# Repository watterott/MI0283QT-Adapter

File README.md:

# MI0283QT-Adapter
Adapter Board with 2.8" TFT-Display and Touchscreen/Touchpanel.

* Multi-Inno MI0283QT 2.8" Display with Touchpanel (320x240 pixel)
* Backlight dimmable
* 3.3V - 5V tolerant IOs
* Power: 3.3V - 5V
* **MI0283QT-Adapter v1**
  * TI ADS7846/TSC2046 Touch-Controller
  * Interface: SPI/SSI (8-Bit or 9-Bit, up to 32MHz)
* **MI0283QT-Adapter v2**
  * NXP LPC1114 ARM Cortex-M0 with Open-Source Firmware
  * Interface: UART, I2C, SPI/SSI (8-Bit, Mode 3, up to 4MHz)
  * Pin-compatible with MI0283QT-Adapter v1
* Open-Source and released under the [Creative Commons Attribution Share-Alike License](https://creativecommons.org/licenses/by-sa/4.0/).
* **[Documentation on learn.watterott.com](https://learn.watterott.com)**

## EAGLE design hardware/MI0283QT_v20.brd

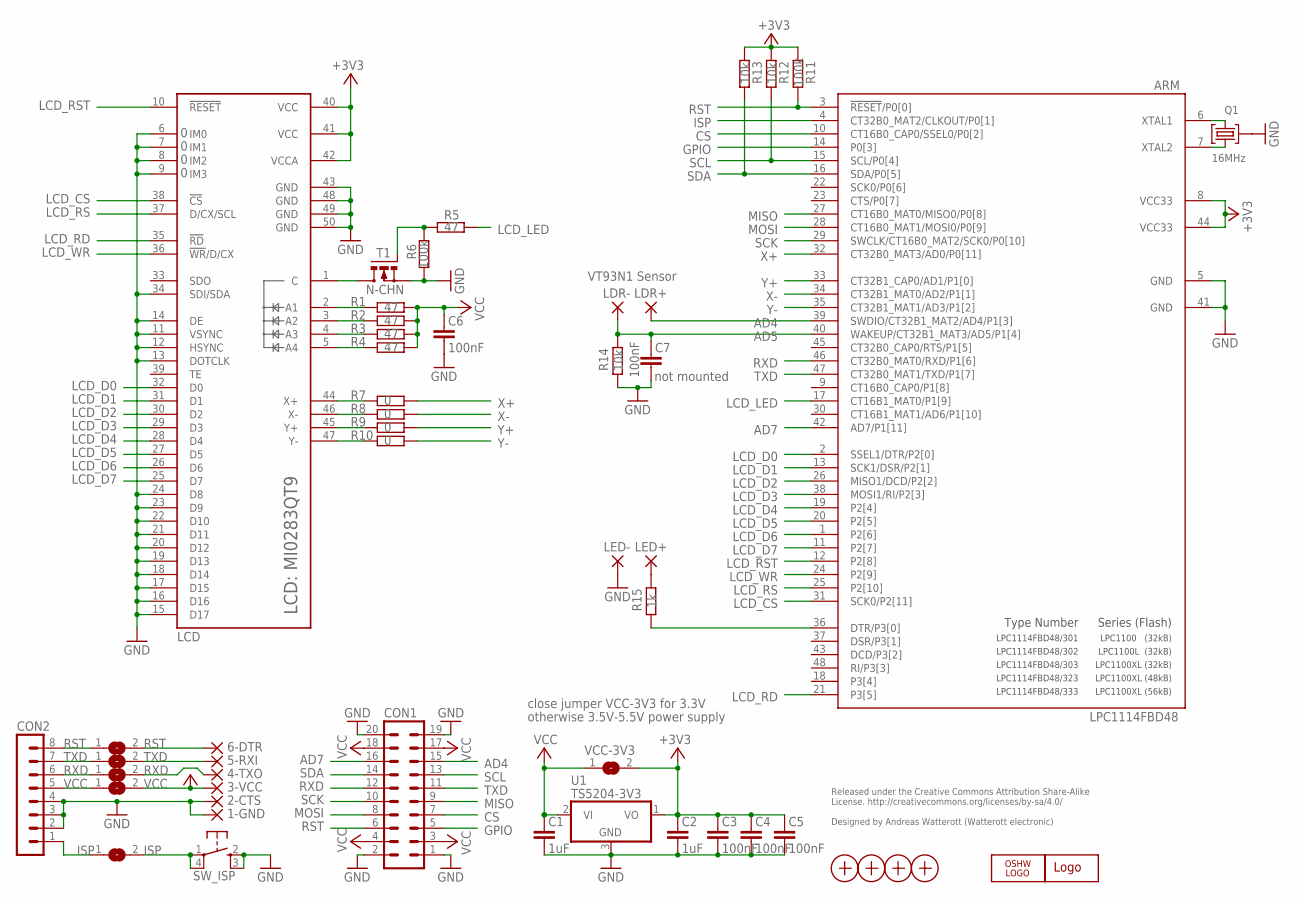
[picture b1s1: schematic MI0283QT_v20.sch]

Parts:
1-GND, 2-CTS, 3-VCC, 4-TXO, 5-RXI, 6-DTR: WIREPADSMD1,27-254; SMD1,27-2,54
ARM: LPC1114FBD48; LQFP48
C1, C2: 1uF; C0603
C3, C4, C5, C6, C7: 100nF; C0603
CON1: MA10-2
CON2: MA08-1
ISP: SJ
LCD: MI0283QT9
LDR+: WIREPAD2,15/1,0; 2,15/1,0
LDR-: WIREPAD2,15/1,0; 2,15/1,0
LED+: WIREPAD2,15/1,0; 2,15/1,0
LED-: WIREPAD2,15/1,0; 2,15/1,0
LOGO1: OSHW_LOGO_6MILX0150-NT; OSHW_6X150_NOTEXT
Q1: 16MHz; SMD_OSC_35X15
R1, R2, R3, R4, R5: 47; R0603
R6, R11: 100k; R0603
R7, R8, R9, R10: 0; R0603
R12, R13, R14: 10k; R0603
R15: 1k; R0603
RST: SJ
RXD: SJ
SW_ISP: SW_SMDS; SW_SMD4@1
T1: N-CHN; MICRO3
TXD: SJ
U1: TS5204-3V3; SOT23
U$1: WE-LOGO
VCC: SJ
VCC-3V3: SJ
X1, X2, X3, X4: PASSER

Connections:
+3V3: ARM.8 (VCC33), ARM.44 (VCC33), C2.1, C3.1, C4.1, C5.1, LCD.40 (VCC), LCD.41 (VCC), LCD.42 (VCCA), R11.2, R12.2, R13.2, U1.1 (VO), VCC-3V3.2
AD4: ARM.39 (SWDIO/CT32B1_MAT2/AD4/P1[3]), CON1.15, LDR+.1
AD5: ARM.40 (WAKEUP/CT32B1_MAT3/AD5/P1[4]), C7.1, LDR-.1, R14.2
AD7: ARM.42 (AD7/P1[11]), CON1.16
C: LCD.1 (C), T1.3 (D)
CS: ARM.10 (CT16B0_CAP0/SSEL0/P0[2]), CON1.7
C_ISP: CON2.1, ISP.1
C_RST: CON2.8, RST.1
C_RXD: CON2.6, RXD.1
C_TXD: CON2.7, TXD.1
C_VCC: CON2.5, VCC.1
GND: 1-GND.1, 2-CTS.1, ARM.5 (GND), ARM.41 (GND), C1.2, C2.2, C3.2, C4.2, C5.2, C6.2, C7.2, CON1.1, CON1.2, CON1.19, CON1.20, CON2.2, CON2.3, CON2.4, LCD.6 (IM0), LCD.7 (IM1), LCD.8 (IM2), LCD.9 (IM3), LCD.11 (VSYNC), LCD.12 (HSYNC), LCD.13 (DOTCLK), LCD.14 (DE), LCD.15 (D17), LCD.16 (D16), LCD.17 (D15), LCD.18 (D14), LCD.19 (D13), LCD.20 (D12), LCD.21 (D11), LCD.22 (D10), LCD.23 (D9), LCD.24 (D8), LCD.34 (SDI/SDA), LCD.43 (GND), LCD.48 (GND), LCD.49 (GND), LCD.50 (GND), LED-.1, Q1.GND, R6.2, R14.1, SW_ISP.2 (S), SW_ISP.3 (S1), T1.2 (S), U1.3 (GND)
GPIO: ARM.14 (P0[3]), CON1.5
ISP: ARM.4 (CT32B0_MAT2/CLKOUT/P0[1]), ISP.2, SW_ISP.1, SW_ISP.4 (P1)
LCD_CS: ARM.31 (SCK0/P2[11]), LCD.38 (!CS)
LCD_D0: ARM.2 (SSEL1/DTR/P2[0]), LCD.32 (D0)
LCD_D1: ARM.13 (SCK1/DSR/P2[1]), LCD.31 (D1)
LCD_D2: ARM.26 (MISO1/DCD/P2[2]), LCD.30 (D2)
LCD_D3: ARM.38 (MOSI1/RI/P2[3]), LCD.29 (D3)
LCD_D4: ARM.19 (P2[4]), LCD.28 (D4)
LCD_D5: ARM.20 (P2[5]), LCD.27 (D5)
LCD_D6: ARM.1 (P2[6]), LCD.26 (D6)
LCD_D7: ARM.11 (P2[7]), LCD.25 (D7)
LCD_LED: ARM.17 (CT16B1_MAT0/P1[9]), R5.2
LCD_RD: ARM.21 (P3[5]), LCD.35 (!RD)
LCD_RS: ARM.25 (P2[10]), LCD.37 (D/CX/SCL)
LCD_RST: ARM.12 (P2[8]), LCD.10 (!RESET)
LCD_WR: ARM.24 (P2[9]), LCD.36 (!WR!/D/CX)
LED: ARM.36 (DTR/P3[0]), R15.1
LEDPWM: R5.1, R6.1, T1.1 (G)
LED_A1: LCD.2 (A1), R1.1
LED_A2: LCD.3 (A2), R2.1
LED_A3: LCD.4 (A3), R3.1
LED_A4: LCD.5 (A4), R4.1
MISO: ARM.27 (CT16B0_MAT0/MISO0/P0[8]), CON1.9
MOSI: ARM.28 (CT16B0_MAT1/MOSI0/P0[9]), CON1.8
unnamed: ARM.6 (XTAL1), Q1.2
unnamed: ARM.7 (XTAL2), Q1.1
unnamed: LED+.1, R15.2
RST: 6-DTR.1, ARM.3 (!RESET!/P0[0]), CON1.6, R11.1, RST.2
RXD: 4-TXO.1, ARM.46 (CT32B0_MAT0/RXD/P1[6]), CON1.12, RXD.2
SCK: ARM.29 (SWCLK/CT16B0_MAT2/SCK0/P0[10]), CON1.10
SCL: ARM.15 (SCL/P0[4]), CON1.13, R12.1
SDA: ARM.16 (SDA/P0[5]), CON1.14, R13.1
TXD: 5-RXI.1, ARM.47 (CT32B0_MAT1/TXD/P1[7]), CON1.11, TXD.2
VCC: 3-VCC.1, C1.1, C6.1, CON1.3, CON1.4, CON1.17, CON1.18, R1.2, R2.2, R3.2, R4.2, U1.2 (VI), VCC.2, VCC-3V3.1
X+: ARM.32 (CT32B0_MAT3/AD0/P0[11]), R7.2
X-: ARM.34 (CT32B1_MAT0/AD2/P1[1]), R8.2
XM: LCD.46 (X-), R8.1
XP: LCD.44 (X+), R7.1
Y+: ARM.33 (CT32B1_CAP0/AD1/P1[0]), R9.2
Y-: ARM.35 (CT32B1_MAT1/AD3/P1[2]), R10.2
YM: LCD.47 (Y-), R10.1
YP: LCD.45 (Y+), R9.1

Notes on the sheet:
Released under the Creative Commons Attribution Share-Alike License. http://creativecommons.org/licenses/by-sa/4.0/ Designed by Andreas Watterott (Watterott electronic)
LPC1100 (32kB)
LPC1100L (32kB)
LPC1100XL (32kB)
LPC1100XL (48kB)
LPC1100XL (56kB)
Type Number
Series (Flash)
LPC1114FBD48/301
LPC1114FBD48/302
LPC1114FBD48/303
LPC1114FBD48/323
LPC1114FBD48/333
not mounted
VT93N1 Sensor
otherwise 3.5V-5.5V power supply
close jumper VCC-3V3 for 3.3V

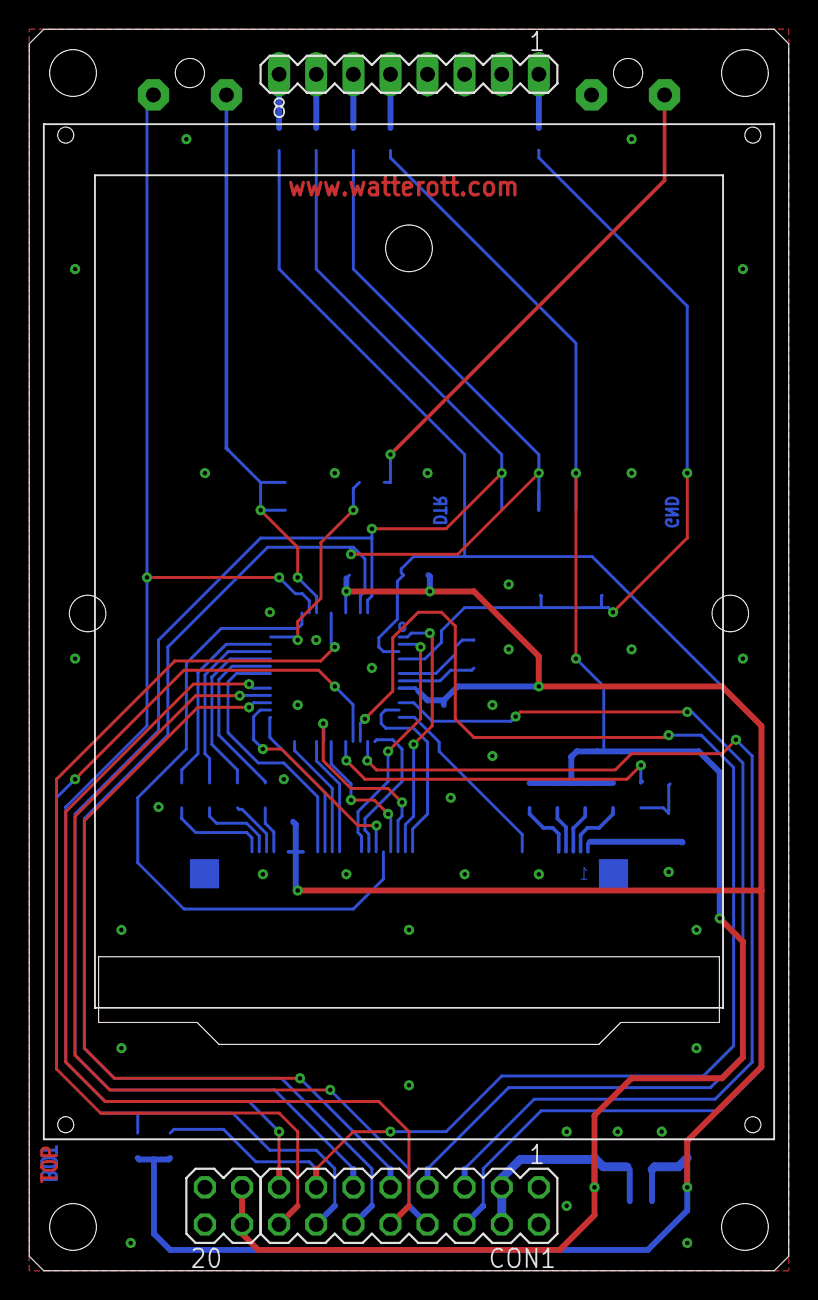
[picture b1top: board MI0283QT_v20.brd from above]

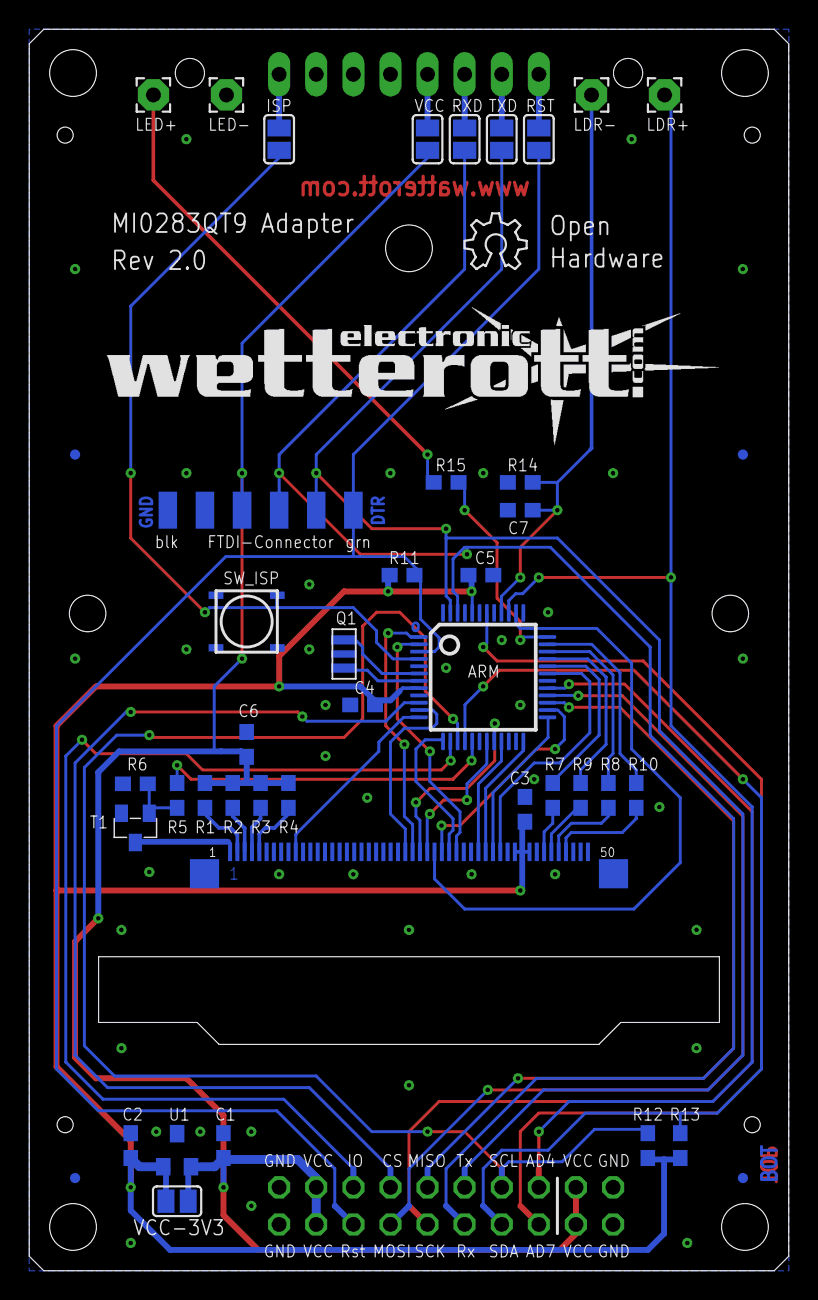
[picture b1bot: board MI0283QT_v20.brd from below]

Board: 2 copper layers, 52.0 x 85.0 mm, 52 parts (49 on the bottom side), 54 nets.

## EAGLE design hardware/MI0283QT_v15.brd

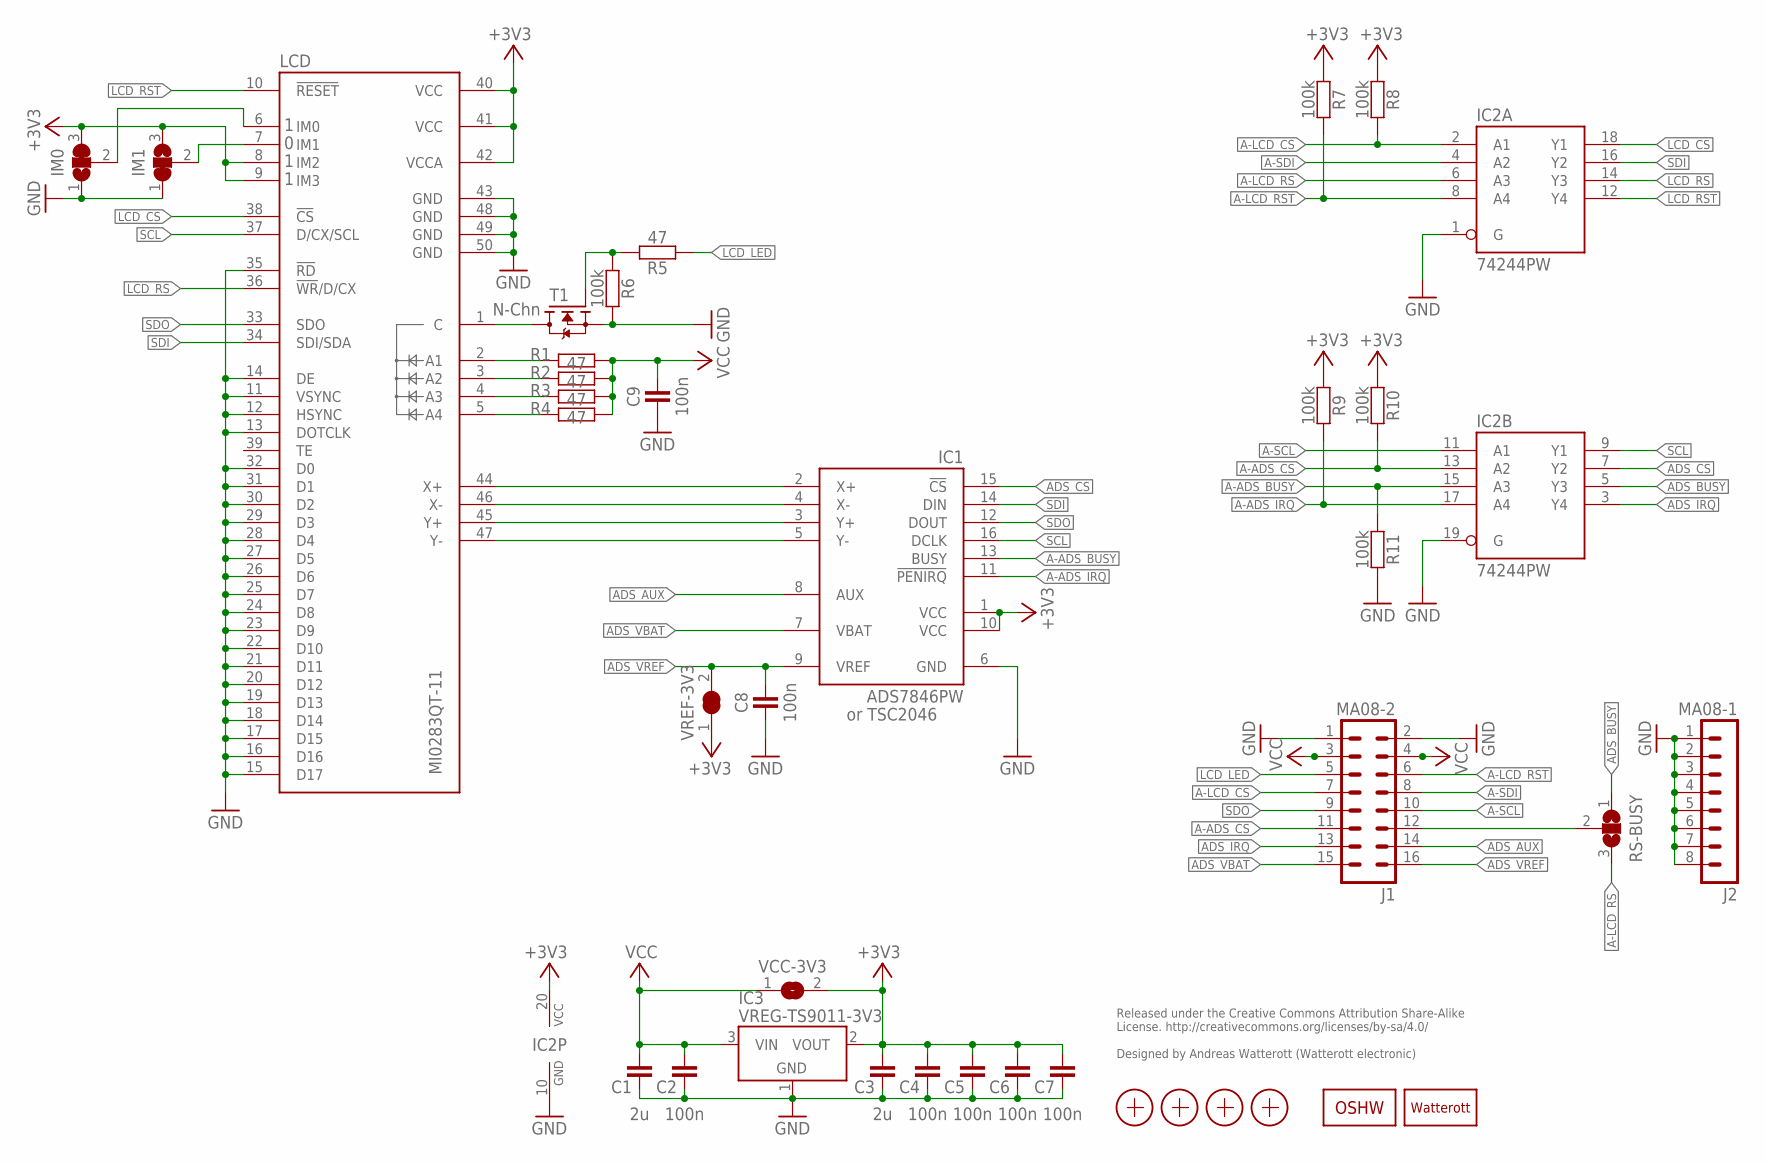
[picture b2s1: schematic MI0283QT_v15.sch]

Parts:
C1, C3: 2u; C0603
C2, C4, C5, C6, C7, C8, C9: 100n; C0402
IC1: ADS7846PW; TSSOP16
IC2: 74244PW; TSSOP20
IC3: VREG-TS9011-3V3; SOT23
IM0, IM1: JUMPER3-0603
J1: MA08-2
J2: MA08-1
LCD: MI0283QT-11; MI0283QT11
LOGO2: OSHW_LOGOX0150; OSHW_6X150
LOGO3: LOGO-PLACE; LOGO_TPLACE
R1, R2, R3, R4, R5: 47; C0402
R6, R7, R8, R9, R10, R11: 100k; C0402
RS-BUSY: JUMPER3-0603
T1: N-Chn; SOT23
VCC-3V3: JUMPER2-0603-NC; JUMPER2-0603_NC
VREF-3V3: JUMPER2-0603-NC; JUMPER2-0603_NC
X1, X2, X3, X4: PASSER-07; PASSER_07MM

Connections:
+3V3: C3.2, C4.2, C5.2, C6.2, C7.2, IC1.1 (VCC), IC1.10 (VCC), IC2.20 (VCC), IC3.2 (VOUT), IM0.3, IM1.3, LCD.8 (IM2), LCD.9 (IM3), LCD.40 (VCC), LCD.41 (VCC), LCD.42 (VCCA), R7.1, R8.1, R9.1, R10.1, VCC-3V3.2, VREF-3V3.1
A-ADS_BUSY: IC1.13 (BUSY), IC2.15 (A3), R11.1
A-ADS_CS: IC2.13 (A2), J1.11, R10.2
A-ADS_IRQ: IC1.11 (!PENIRQ), IC2.17 (A4), R9.2
A-LCD_CS: IC2.2 (A1), J1.7, R8.2
A-LCD_RS: IC2.6 (A3), RS-BUSY.3
A-LCD_RST: IC2.8 (A4), J1.6, R7.2
A-SCL: IC2.11 (A1), J1.10
A-SDI: IC2.4 (A2), J1.8
ADS_AUX: IC1.8 (AUX), J1.14
ADS_BUSY: IC2.5 (Y3), RS-BUSY.1
ADS_CS: IC1.15 (!CS), IC2.7 (Y2)
ADS_IRQ: IC2.3 (Y4), J1.13
ADS_VBAT: IC1.7 (VBAT), J1.15
ADS_VREF: C8.2, IC1.9 (VREF), J1.16, VREF-3V3.2
BUSY_RS: J1.12, RS-BUSY.2
C: LCD.1 (C), T1.3 (D)
GND: C1.1, C2.1, C3.1, C4.1, C5.1, C6.1, C7.1, C8.1, C9.1, IC1.6 (GND), IC2.1 (G), IC2.10 (GND), IC2.19 (G), IC3.1 (GND), IM0.1, IM1.1, J1.1, J1.2, J2.1, J2.2, J2.3, J2.4, J2.5, J2.6, J2.7, J2.8, LCD.11 (VSYNC), LCD.12 (HSYNC), LCD.13 (DOTCLK), LCD.14 (DE), LCD.15 (D17), LCD.16 (D16), LCD.17 (D15), LCD.18 (D14), LCD.19 (D13), LCD.20 (D12), LCD.21 (D11), LCD.22 (D10), LCD.23 (D9), LCD.24 (D8), LCD.25 (D7), LCD.26 (D6), LCD.27 (D5), LCD.28 (D4), LCD.29 (D3), LCD.30 (D2), LCD.31 (D1), LCD.32 (D0), LCD.35 (!RD), LCD.43 (GND), LCD.48 (GND), LCD.49 (GND), LCD.50 (GND), R6.2, R11.2, T1.2 (S)
IM0: IM0.2, LCD.6 (IM0)
LCD_CS: IC2.18 (Y1), LCD.38 (!CS)
LCD_LED: J1.5, R5.1
LCD_RS: IC2.14 (Y3), LCD.36 (!WR!/D/CX)
LCD_RST: IC2.12 (Y4), LCD.10 (!RESET)
LEDPWM: R5.2, R6.1, T1.1 (G)
LED_A1: LCD.2 (A1), R1.2
LED_A2: LCD.3 (A2), R2.2
LED_A3: LCD.4 (A3), R3.2
LED_A4: LCD.5 (A4), R4.2
unnamed: IC1.5 (Y-), LCD.47 (Y-)
unnamed: IC1.3 (Y+), LCD.45 (Y+)
unnamed: IC1.4 (X-), LCD.46 (X-)
unnamed: IC1.2 (X+), LCD.44 (X+)
unnamed: IM1.2, LCD.7 (IM1)
SCL: IC1.16 (DCLK), IC2.9 (Y1), LCD.37 (D/CX/SCL)
SDI: IC1.14 (DIN), IC2.16 (Y2), LCD.34 (SDI/SDA)
SDO: IC1.12 (DOUT), J1.9, LCD.33 (SDO)
VCC: C1.2, C2.2, C9.2, IC3.3 (VIN), J1.3, J1.4, R1.1, R2.1, R3.1, R4.1, VCC-3V3.1

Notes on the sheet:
Released under the Creative Commons Attribution Share-Alike License. http://creativecommons.org/licenses/by-sa/4.0/ Designed by Andreas Watterott (Watterott electronic)
or TSC2046

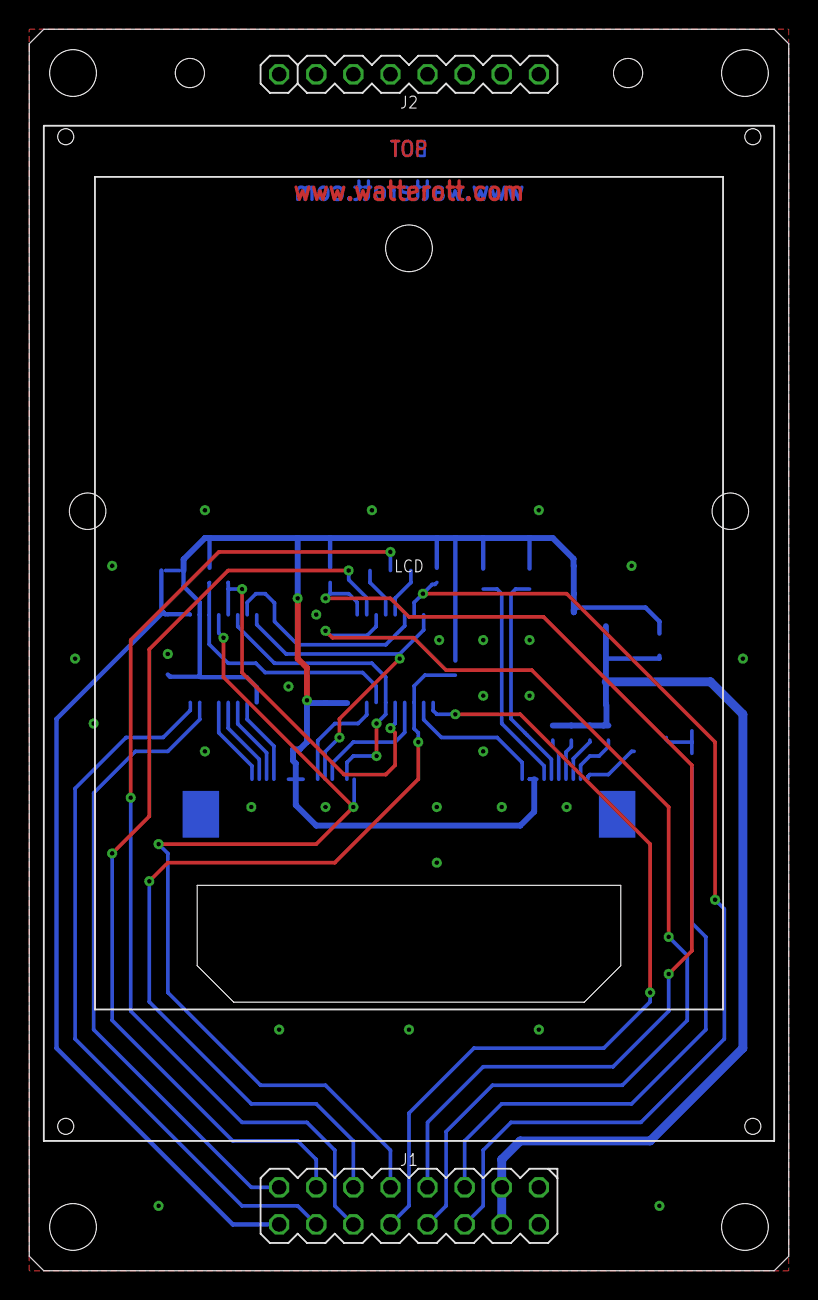
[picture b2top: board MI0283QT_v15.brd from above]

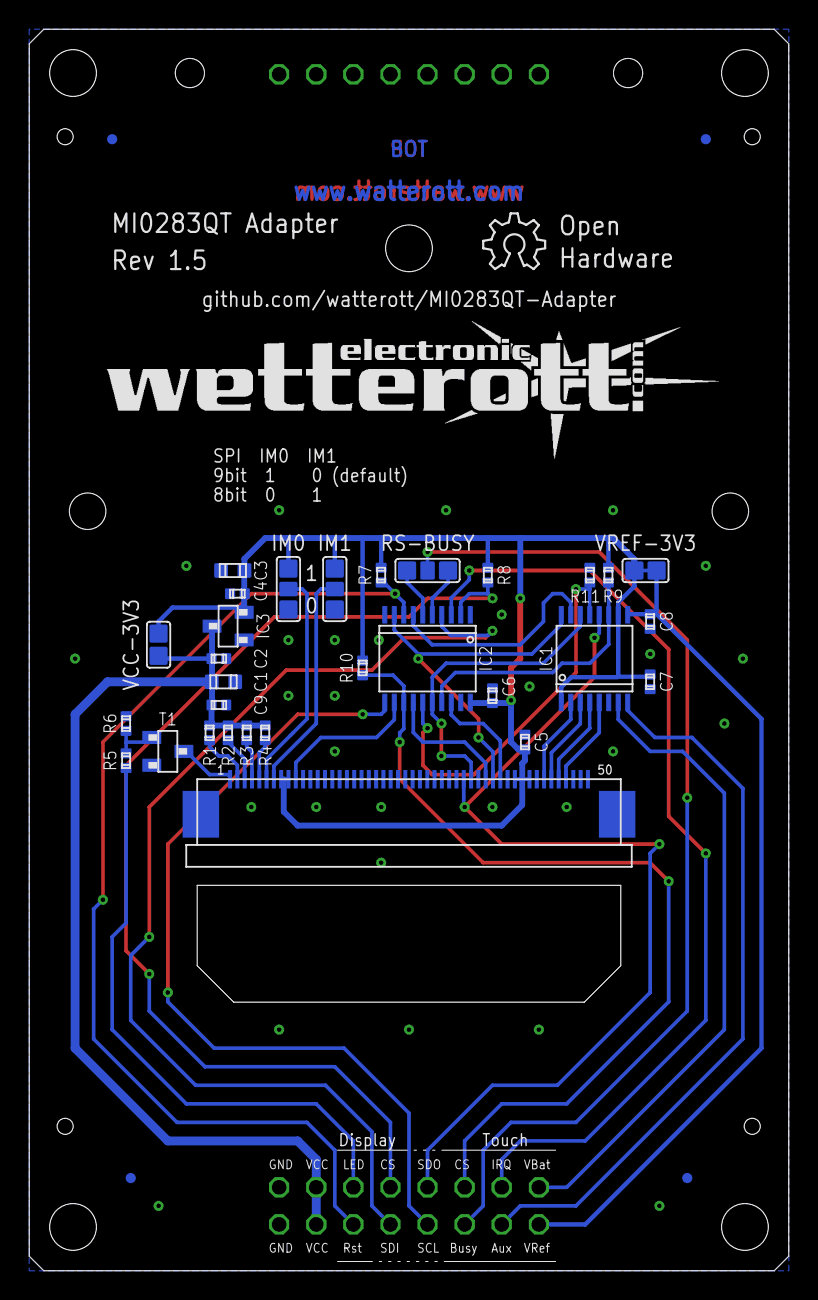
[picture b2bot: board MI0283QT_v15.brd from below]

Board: 2 copper layers, 52.0 x 85.0 mm, 38 parts (35 on the bottom side), 37 nets.

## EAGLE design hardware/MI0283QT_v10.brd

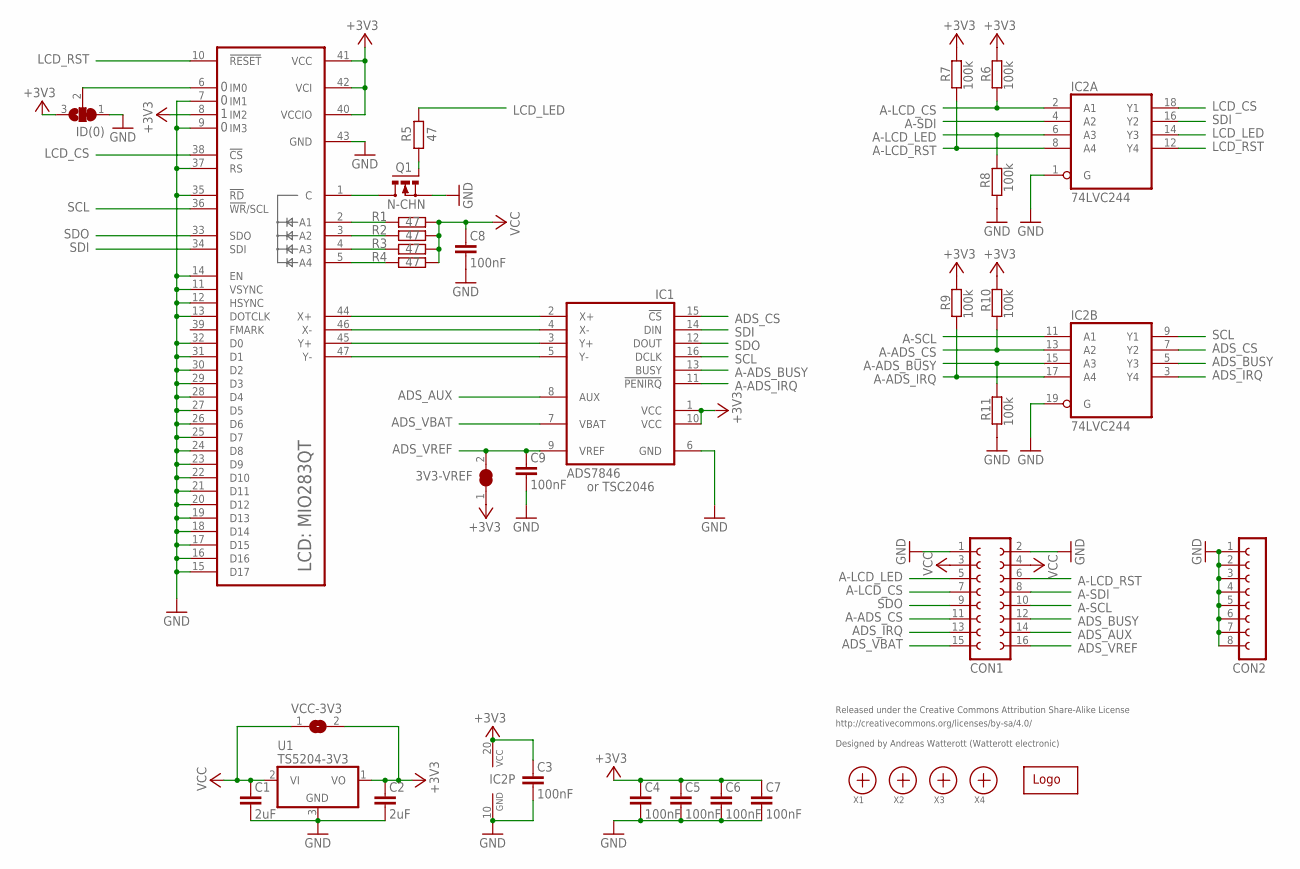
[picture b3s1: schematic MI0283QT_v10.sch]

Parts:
3V3-VREF: SJ
C1, C2: 2uF; C0805
C3, C4, C5, C6, C7, C8, C9: 100nF; C0603
CON1: FE08-2
CON2: FE08-1; FE08
IC1: ADS7846; SSOP16
IC2: 74LVC244; SO20W
ID(0): SJ2W; SJ_2
LCD: MI0283QT
Q1: N-CHN; MICRO3
R1, R2, R3, R4, R5: 47; R0603
R6, R7, R8, R9, R10, R11: 100k; R0603
U1: TS5204-3V3; SOT23
U$1: WE-LOGO
VCC-3V3: SJ
X1, X2, X3, X4: PASSER

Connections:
+3V3: 3V3-VREF.1, C2.1, C3.1, C4.1, C5.1, C6.1, C7.1, IC1.1 (VCC), IC1.10 (VCC), IC2.20 (VCC), ID(0).3, LCD.8 (IM2), LCD.40 (VCCIO), LCD.41 (VCC), LCD.42 (VCI), R6.2, R7.2, R9.2, R10.2, U1.1 (VO), VCC-3V3.2
A-ADS_BUSY: IC1.13 (BUSY), IC2.15 (A3), R11.1
A-ADS_CS: CON1.11, IC2.13 (A2), R10.1
A-ADS_IRQ: IC1.11 (!PENIRQ), IC2.17 (A4), R9.1
A-LCD_CS: CON1.7, IC2.2 (A1), R6.1
A-LCD_LED: CON1.5, IC2.6 (A3), R8.1
A-LCD_RST: CON1.6, IC2.8 (A4), R7.1
A-SCL: CON1.10, IC2.11 (A1)
A-SDI: CON1.8, IC2.4 (A2)
ADS_AUX: CON1.14, IC1.8 (AUX)
ADS_BUSY: CON1.12, IC2.5 (Y3)
ADS_CS: IC1.15 (!CS), IC2.7 (Y2)
ADS_IRQ: CON1.13, IC2.3 (Y4)
ADS_VBAT: CON1.15, IC1.7 (VBAT)
ADS_VREF: 3V3-VREF.2, C9.1, CON1.16, IC1.9 (VREF)
C: LCD.1 (C), Q1.3 (D)
GND: C1.2, C2.2, C3.2, C4.2, C5.2, C6.2, C7.2, C8.2, C9.2, CON1.1, CON1.2, CON2.1, CON2.2, CON2.3, CON2.4, CON2.5, CON2.6, CON2.7, CON2.8, IC1.6 (GND), IC2.1 (G), IC2.10 (GND), IC2.19 (G), ID(0).1, LCD.7 (IM1), LCD.9 (IM3), LCD.11 (VSYNC), LCD.12 (HSYNC), LCD.13 (DOTCLK), LCD.14 (EN), LCD.15 (D17), LCD.16 (D16), LCD.17 (D15), LCD.18 (D14), LCD.19 (D13), LCD.20 (D12), LCD.21 (D11), LCD.22 (D10), LCD.23 (D9), LCD.24 (D8), LCD.25 (D7), LCD.26 (D6), LCD.27 (D5), LCD.28 (D4), LCD.29 (D3), LCD.30 (D2), LCD.31 (D1), LCD.32 (D0), LCD.35 (!RD), LCD.37 (RS), LCD.43 (GND), Q1.2 (S), R8.2, R11.2, U1.3 (GND)
IM0: ID(0).2, LCD.6 (IM0)
LCD_CS: IC2.18 (Y1), LCD.38 (!CS)
LCD_LED: IC2.14 (Y3), R5.2
LCD_RST: IC2.12 (Y4), LCD.10 (!RESET)
LEDPWM: Q1.1 (G), R5.1
LED_A1: LCD.2 (A1), R1.1
LED_A2: LCD.3 (A2), R2.1
LED_A3: LCD.4 (A3), R3.1
LED_A4: LCD.5 (A4), R4.1
SCL: IC1.16 (DCLK), IC2.9 (Y1), LCD.36 (!WR!/SCL)
SDI: IC1.14 (DIN), IC2.16 (Y2), LCD.34 (SDI)
SDO: CON1.9, IC1.12 (DOUT), LCD.33 (SDO)
VCC: C1.1, C8.1, CON1.3, CON1.4, R1.2, R2.2, R3.2, R4.2, U1.2 (VI), VCC-3V3.1
X+: IC1.2 (X+), LCD.44 (X+)
X-: IC1.4 (X-), LCD.46 (X-)
Y+: IC1.3 (Y+), LCD.45 (Y+)
Y-: IC1.5 (Y-), LCD.47 (Y-)

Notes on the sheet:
Released under the Creative Commons Attribution Share-Alike License
http://creativecommons.org/licenses/by-sa/4.0/
Designed by Andreas Watterott (Watterott electronic)
or TSC2046

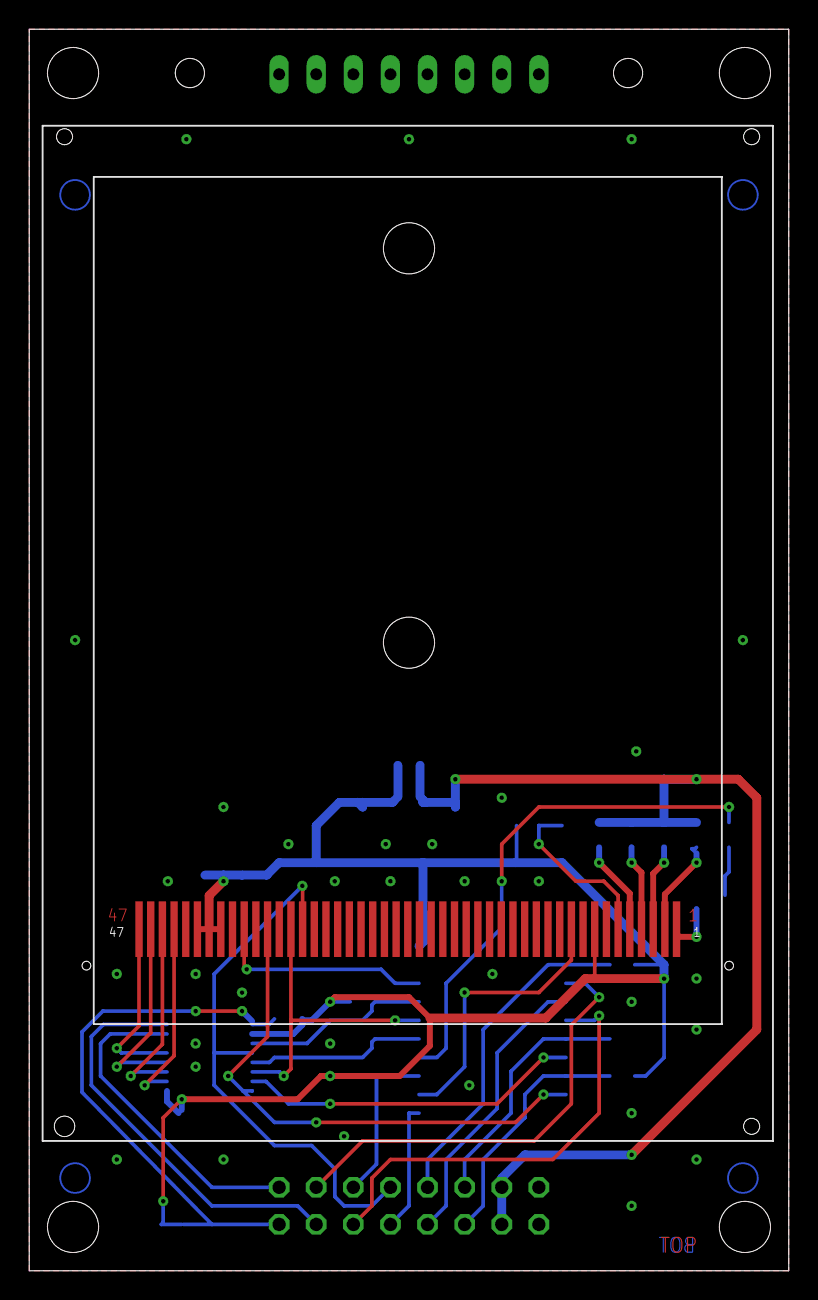
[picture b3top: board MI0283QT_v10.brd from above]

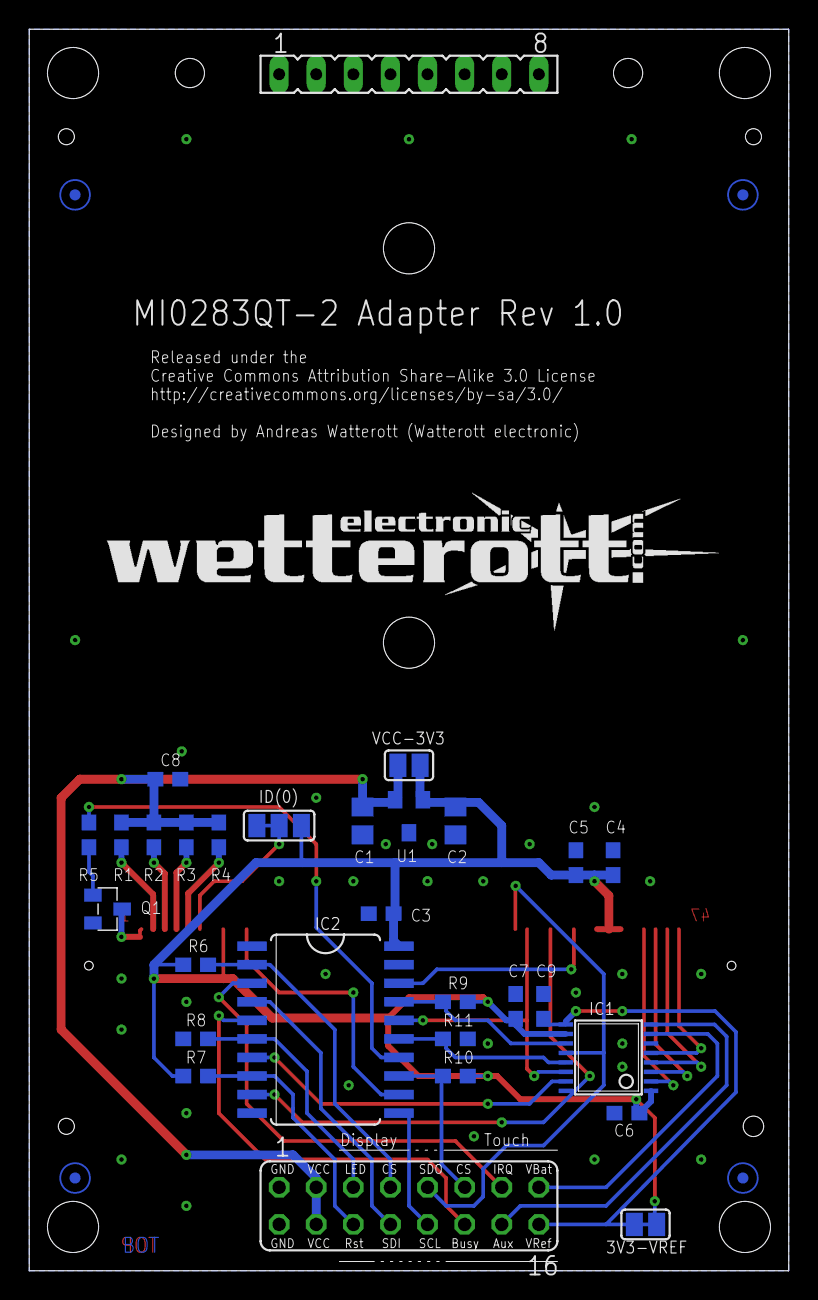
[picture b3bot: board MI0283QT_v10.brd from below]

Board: 2 copper layers, 52.0 x 85.0 mm, 35 parts (34 on the bottom side), 34 nets.

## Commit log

2012-03-13 updated readme added layout files and images
2012-04-01 clean-up of schematics
2013-02-21 added MI0283QT9A schematics + layout
2013-03-11 added project list
2013-03-16 updated projects
2013-03-21 added pinout to size diagram updated readme and project list
2013-05-27 added v2 infos and schematics
2013-06-17 updated projects and readme
2013-06-17 added v2 schematics and layout
2013-06-17 added firmware
2013-06-17 added fw docu
2013-06-22 added infos to schematics
2013-06-22 Firmware v0.02
2013-06-22 moved CON2 to bottom
2013-06-25 updated docu and examples
2013-06-26 updated readme and fw docu
2013-06-29 updated fw docu
2013-07-13 fixed interface change time
2013-08-18 updated schematics
2013-08-18 Firmware v0.03
    added byte order setting
    improved lcd routines
2013-08-18 FW v0.03
2013-08-20 updated examples and added nav switch example
2013-08-23 updated fw update guide
2013-09-18 Firmware v0.04
2013-09-19 updated connection overview
2013-09-20 updated image
2013-09-29 added new example
2013-10-01 updated docu, readme, examples
2013-10-17 updated docu
2013-10-17 I2C address mistake
2013-10-26 bug fix in color conversion macros
2013-10-30 updated to CMSIS v3.2
2013-10-30 Building with LPCXpresso IDE possible
2013-11-01 LPCXpresso: use non-floating-point printf
2013-12-09 Firmware v0.05
    added interrupt/status output
    type optimization
2013-12-11 bugfix: orientation was not correctly interpreted in touchpanel functions
2013-12-11 Firmware v0.05 with orientation bugfix
2013-12-12 updated cad files to Eagle xml format
2013-12-12 added new v1.3 schematics and layout
2014-01-02 bugfix in drawtext and drawstring
2014-01-02 Firmware v0.05 with orientation+drawtext bugfix
2014-01-14 updated dimension drawing
2014-02-07 typo
2014-02-07 Bugfix in touch calibration routineBugfix in touch calibration routine
2014-03-10 updated license infos
2014-06-08 Firmware v0.06
2014-06-11 updated license info
2014-06-30 bugfix in set_pwm()
2014-06-30 Firmware v0.07
2014-08-15 updated schematic and layout files
2014-08-21 updated layout and schematics
2014-08-28 removed wrong files
2014-09-26 updated to v0.06
2014-10-09 updated example
2014-10-09 updated to work with CrossWorks v3
2014-10-28 firmware v0.07 with SPI as default interface
2014-11-06 cleaned up schematics and layout
2015-01-10 updated project files
2015-01-10 moved image
2015-01-10 updated reame
2015-01-28 updated license
2015-08-10 updated examples
2015-08-21 changed path structure
2015-12-22 added v1.5
2016-03-03 update schematics
2016-03-07 updated layout
2016-08-28 typo fix
2017-07-30 updated comments
2018-01-30 moved files
2020-07-01 updated PDFs and schematics
2022-01-26 add CMD_LCD_ENABLE + CMD_LCD_DISABLE
2022-02-02 firmware v0.08
2022-02-02 MCUxpresso project file

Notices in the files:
hardware/MI0283QT_v10.brd:
Creative Commons Attribution Share-Alike 3.0 License
http://creativecommons.org/licenses/by-sa/3.0
